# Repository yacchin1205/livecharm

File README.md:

# このリポジトリについて

*TBD*

# 必要パーツ

- Adafruit Feather RP2040 - ¥2,211
  https://www.switch-science.com/catalog/7216/
- リチウムイオンポリマー電池110mAh - ¥1,094
  https://www.switch-science.com/catalog/3166/
- MAX98357A搭載 I2S 3W D級アンプボード - ¥1,309
  https://www.switch-science.com/catalog/2749/
- uxcell オーバル 1W 8オーム マグネットスピーカー 4個 - ¥628
  https://www.amazon.co.jp/gp/product/B017IIV8KM/ 
- KKHMF TTP223 静電容量式 タッチスイッチ 10個 - ¥539
  https://www.amazon.co.jp/gp/product/B079BKVT98/

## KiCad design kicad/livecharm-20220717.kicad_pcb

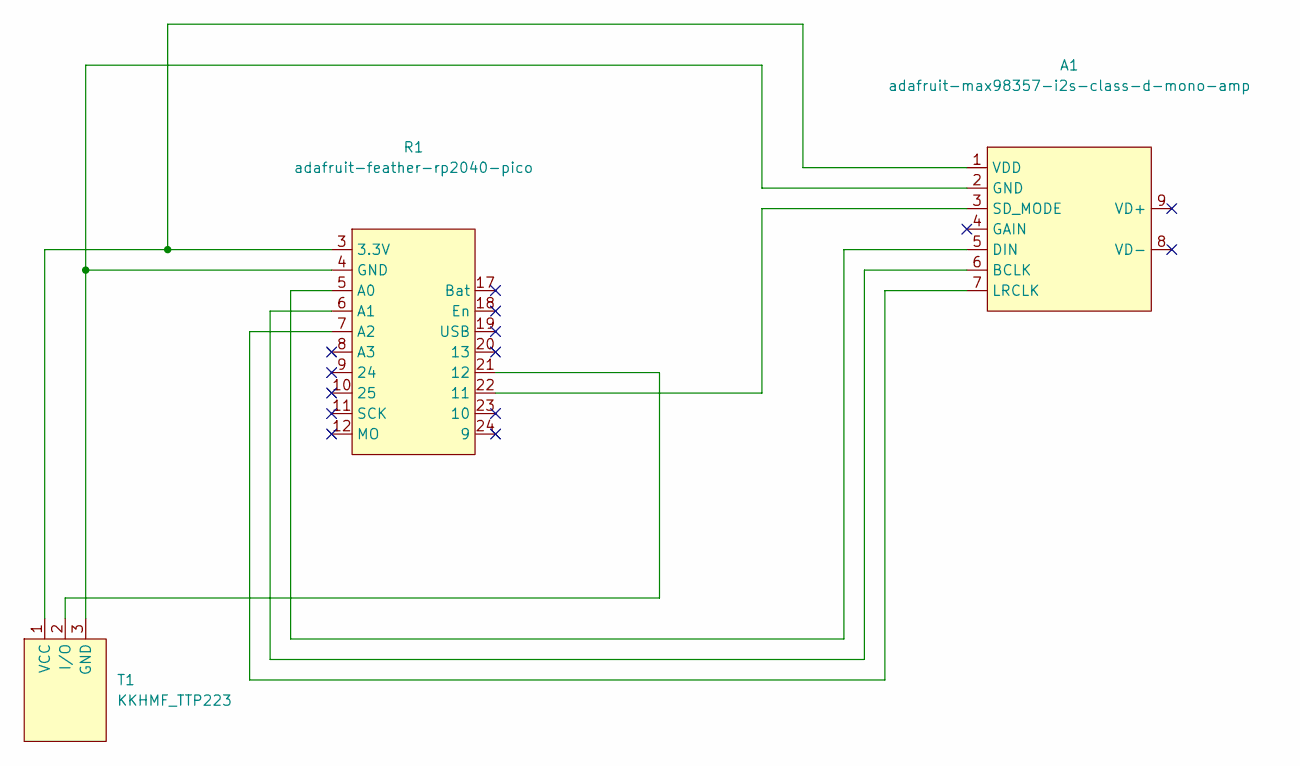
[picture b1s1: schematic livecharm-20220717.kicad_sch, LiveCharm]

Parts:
A1: adafruit-max98357-i2s-class-d-mono-amp
R1: adafruit-feather-rp2040-pico
T1: KKHMF_TTP223

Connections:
unnamed: A1.1 (VDD), R1.3 (3.3V), T1.1 (VCC)
unnamed: A1.2 (GND), R1.4 (GND), T1.3 (GND)
unnamed: A1.3 (SD_MODE), R1.22 (11)
unnamed: A1.5 (DIN), R1.5 (A0)
unnamed: A1.6 (BCLK), R1.6 (A1)
unnamed: A1.7 (LRCLK), R1.7 (A2)
unnamed: R1.21 (12), T1.2 (I/O)

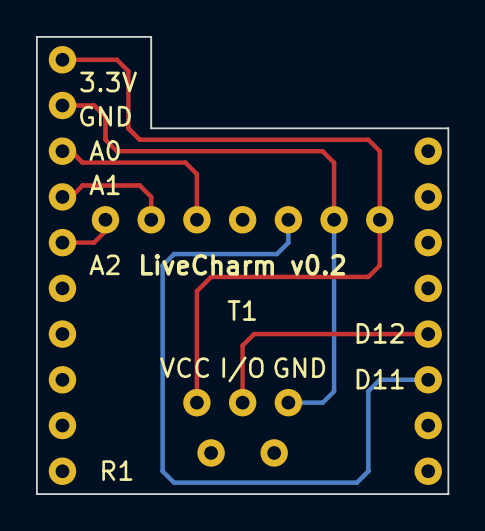
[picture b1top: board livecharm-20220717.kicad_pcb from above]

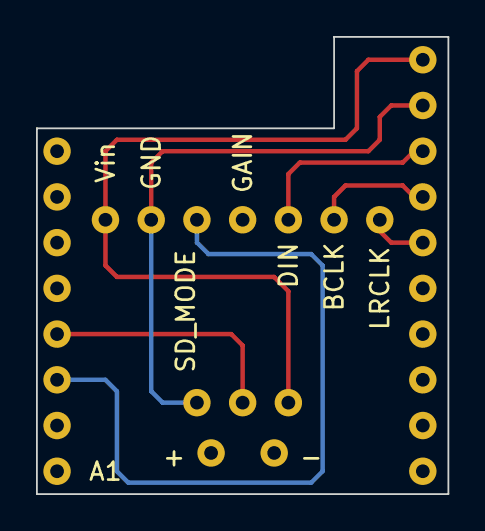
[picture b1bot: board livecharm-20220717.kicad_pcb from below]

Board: 2 copper layers, 22.9 x 25.4 mm, 3 parts (2 on the bottom side), 7 nets.

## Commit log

2022-07-17 Fix alarms
2022-07-17 Fix code
2022-07-31 Refactor scripts
2022-07-31 Add utility script
2022-07-31 Add CAD files
2022-07-31 Add gerber file
2022-07-31 Add README
